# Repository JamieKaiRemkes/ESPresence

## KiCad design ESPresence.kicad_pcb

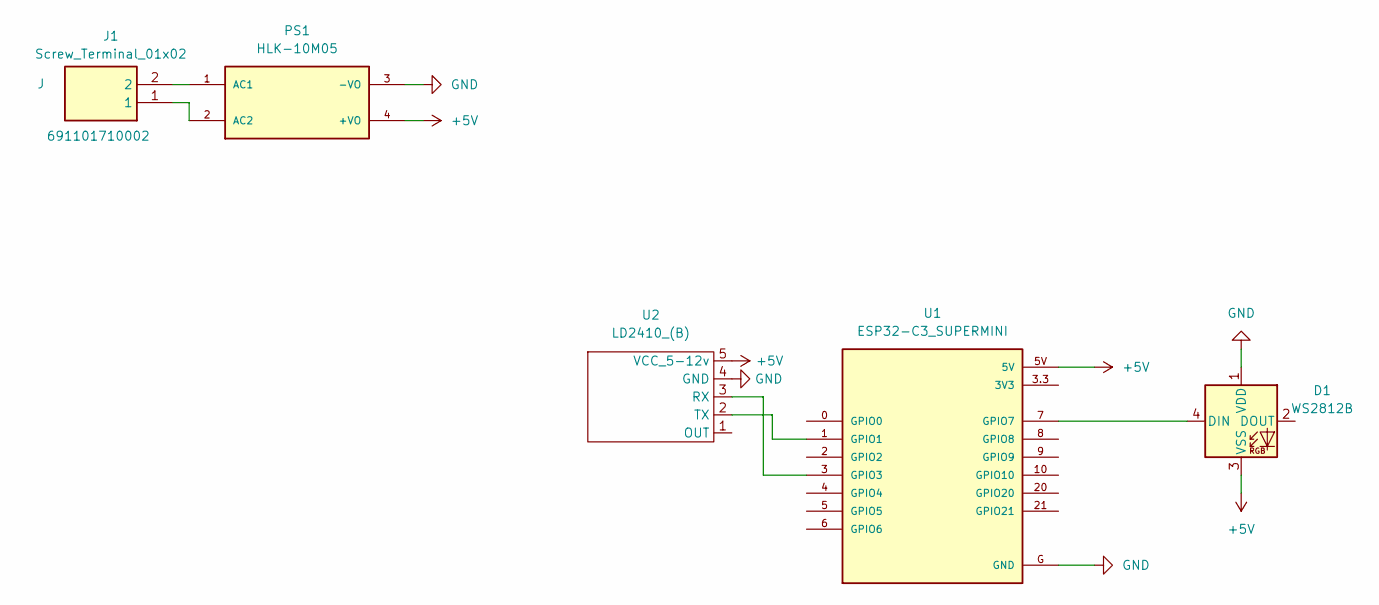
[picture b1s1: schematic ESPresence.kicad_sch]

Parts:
D1: WS2812B; LED_WS2812B_PLCC4_5.0x5.0mm_P3.2mm
J1: Screw_Terminal_01x02; RHDRRA2W95P0X500_1X2_1120X900X1280P; Mouser Part Number 710-691101710002
PS1: HLK-10M05; PARTREV V1.8
U1: ESP32-C3_SUPERMINI
U2: LD2410_(B); LD2410 (B)

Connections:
+5V: D1.3 (VSS), PS1.4 (+VO), U1.5V, U2.5 (VCC_5-12v)
GND: D1.1 (VDD), PS1.3 (-VO), U1.G (GND), U2.4 (GND)
unnamed: J1.2, PS1.1 (AC1)
unnamed: J1.1, PS1.2 (AC2)
unnamed: U1.1 (GPIO1), U2.2 (TX)
unnamed: U1.3 (GPIO3), U2.3 (RX)
unnamed: D1.4 (DIN), U1.7 (GPIO7)

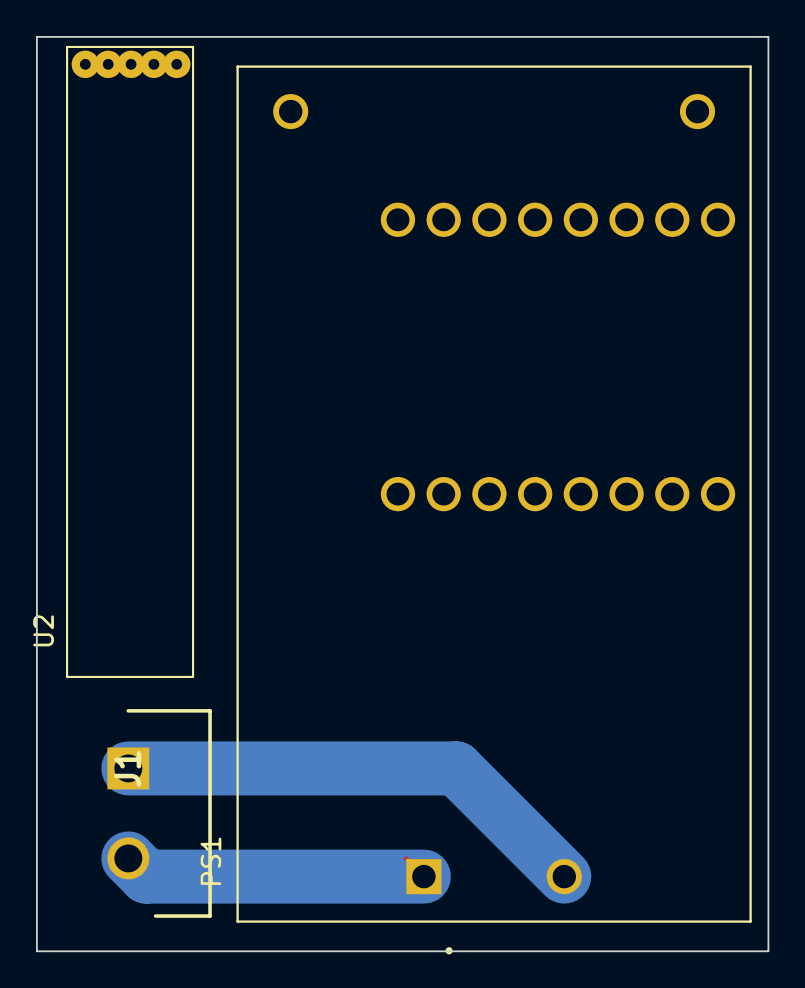
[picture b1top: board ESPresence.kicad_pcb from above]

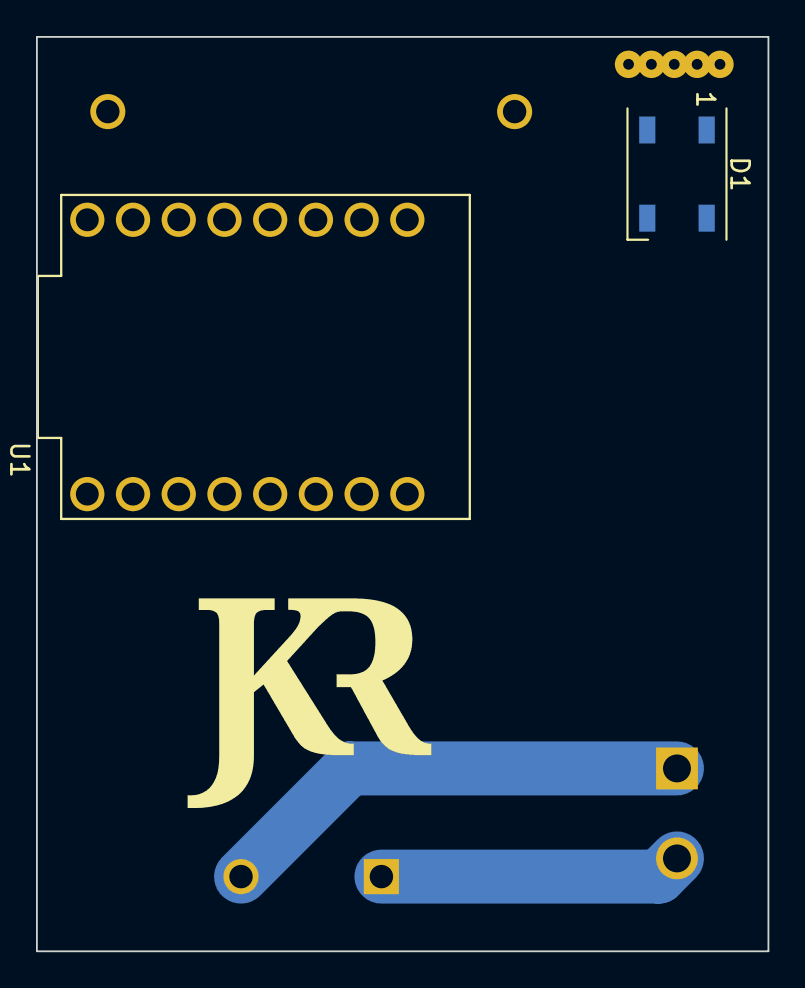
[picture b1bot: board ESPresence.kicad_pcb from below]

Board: 2 copper layers, 40.6 x 50.8 mm, 5 parts (2 on the bottom side), 7 nets.

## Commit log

2023-12-17 feat: initial try out for LD2410 based presence sensor using ESPhome
